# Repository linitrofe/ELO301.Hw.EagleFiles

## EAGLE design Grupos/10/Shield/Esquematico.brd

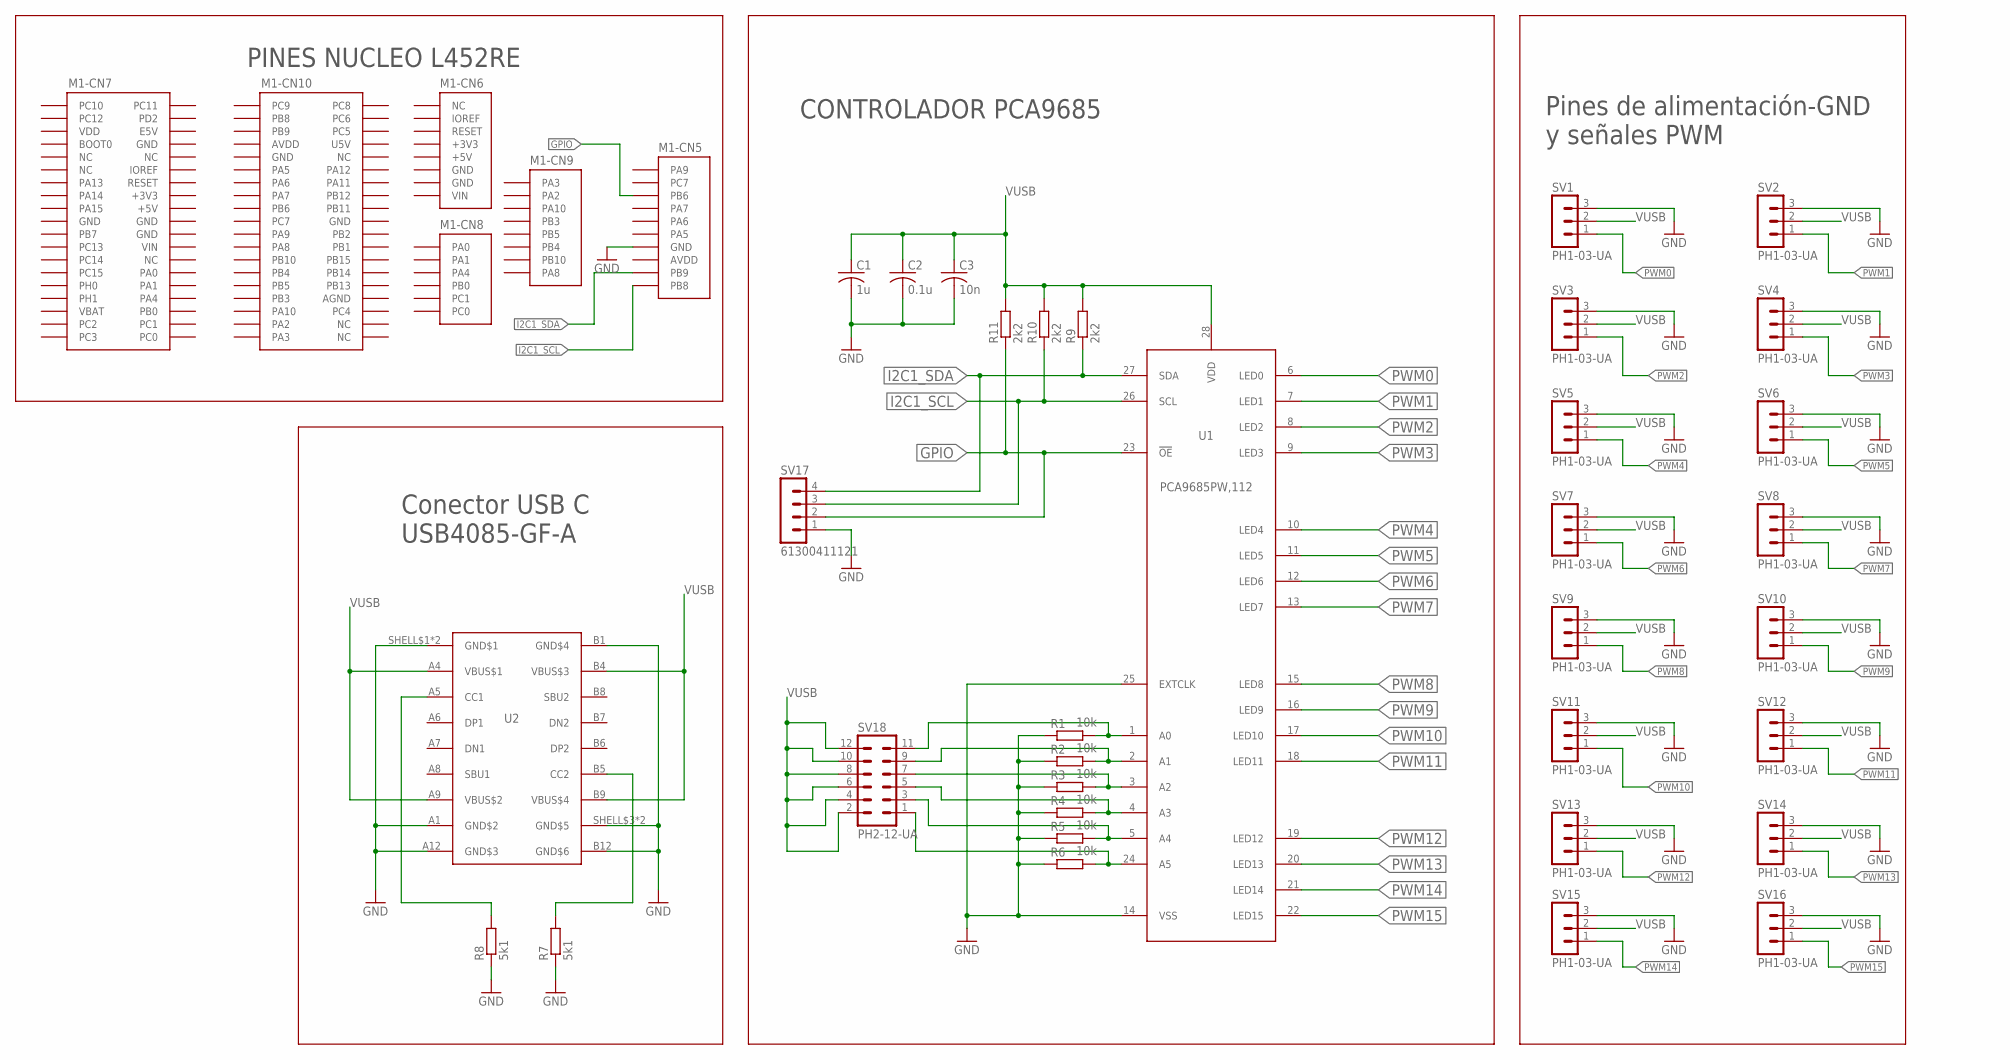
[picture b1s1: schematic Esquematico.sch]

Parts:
C1: 1u; C1206; PARTNO 490-5810-1-ND
C2: 0.1u; C0805; PARTNO 490-GCJ21BR72A104KA01KCT-ND
C3: 10n; C0603; PARTNO 490-4781-1-ND
M1: NUCLEO-L452RE; NUCLEO-64; PARTNO NUCLEO-L452RE
R1, R2, R3, R4, R5, R6: 10k; R0805; PARTNO 311-10KARCT-ND
R7, R8: 5k1; R0805; PARTNO 311-5.10KCRCT-ND
R9, R10, R11: 2k2; R0805; PARTNO 311-2.2KARCT-ND
SV1, SV2, SV3, SV4, SV5, SV6, SV7, SV8, SV9, SV10, SV11, SV12, SV13, SV14, SV15, SV16: PH1-03-UA; MA03-1; PARTNO PH1-03-UA
SV17: 61300411121; MA04-1; PARTNO 61300411121
SV18: PH2-12-UA; MA06-2; PARTNO PH2-12-UA
U1: PCA9685PW,112; SOP65P640X110-28N; PARTNO PCA9685PW,112
U2: USB4085-GF-A; TROUGH_HOLE; PARTNO 2073-USB4085-GF-ACT-ND

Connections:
+3V3: M1.CN6-4 (+3V3), M1.CN7-16 (+3V3)
+5V: M1.CN6-5 (+5V), M1.CN7-18 (+5V)
AGND: M1.CN10-32 (AGND)
AVDD: M1.CN5-8 (AVDD), M1.CN10-7 (AVDD)
GND: C1.2, C2.2, C3.2, M1.CN5-7 (GND), M1.CN6-6 (GND), M1.CN6-7 (GND), M1.CN7-8 (GND), M1.CN7-19 (GND), M1.CN7-20 (GND), M1.CN7-22 (GND), M1.CN10-9 (GND), M1.CN10-20 (GND), R1.1, R2.1, R3.1, R4.1, R5.1, R6.1, R7.1, R8.1, SV1.3, SV2.3, SV3.3, SV4.3, SV5.3, SV6.3, SV7.3, SV8.3, SV9.3, SV10.3, SV11.3, SV12.3, SV13.3, SV14.3, SV15.3, SV16.3, SV17.1, U1.14 (VSS), U1.25 (EXTCLK), U2.A1 (GND$2), U2.A12 (GND$3), U2.B1 (GND$4), U2.B12 (GND$6), U2.SHELL$1 (GND$1), U2.SHELL$2 (GND$1), U2.SHELL$3 (GND$5), U2.SHELL$4 (GND$5)
GPIO: M1.CN5-3 (PB6), R11.1, SV17.2, U1.23 (!OE)
I2C1_SCL: M1.CN5-10 (PB8), R10.1, SV17.3, U1.26 (SCL)
I2C1_SDA: M1.CN5-9 (PB9), R9.1, SV17.4, U1.27 (SDA)
IOREF: M1.CN6-2 (IOREF)
unnamed: R1.2, SV18.11, U1.1 (A0)
unnamed: R2.2, SV18.9, U1.2 (A1)
unnamed: R3.2, SV18.7, U1.3 (A2)
unnamed: R4.2, SV18.5, U1.4 (A3)
unnamed: R5.2, SV18.3, U1.5 (A4)
unnamed: R6.2, SV18.1, U1.24 (A5)
unnamed: R8.2, U2.A5 (CC1)
unnamed: R7.2, U2.B5 (CC2)
PWM0: SV1.1, U1.6 (LED0)
PWM1: SV2.1, U1.7 (LED1)
PWM2: SV3.1, U1.8 (LED2)
PWM3: SV4.1, U1.9 (LED3)
PWM4: SV5.1, U1.10 (LED4)
PWM5: SV6.1, U1.11 (LED5)
PWM6: SV7.1, U1.12 (LED6)
PWM7: SV8.1, U1.13 (LED7)
PWM8: SV9.1, U1.15 (LED8)
PWM9: SV10.1, U1.16 (LED9)
PWM10: SV11.1, U1.17 (LED10)
PWM11: SV12.1, U1.18 (LED11)
PWM12: SV13.1, U1.19 (LED12)
PWM13: SV14.1, U1.20 (LED13)
PWM14: SV15.1, U1.21 (LED14)
PWM15: SV16.1, U1.22 (LED15)
U5V: M1.CN10-8 (U5V)
VBAT: M1.CN7-33 (VBAT)
VDD: M1.CN7-5 (VDD)
VIN: M1.CN6-8 (VIN), M1.CN7-24 (VIN)
VUSB: C1.1, C2.1, C3.1, R9.2, R10.2, R11.2, SV1.2, SV2.2, SV3.2, SV4.2, SV5.2, SV6.2, SV7.2, SV8.2, SV9.2, SV10.2, SV11.2, SV12.2, SV13.2, SV14.2, SV15.2, SV16.2, SV18.2, SV18.4, SV18.6, SV18.8, SV18.10, SV18.12, U1.28 (VDD), U2.A4 (VBUS$1), U2.A9 (VBUS$2), U2.B4 (VBUS$3), U2.B9 (VBUS$4)

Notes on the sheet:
Pines de alimentación-GND y señales PWM
CONTROLADOR PCA9685
PINES NUCLEO L452RE
Conector USB C USB4085-GF-A

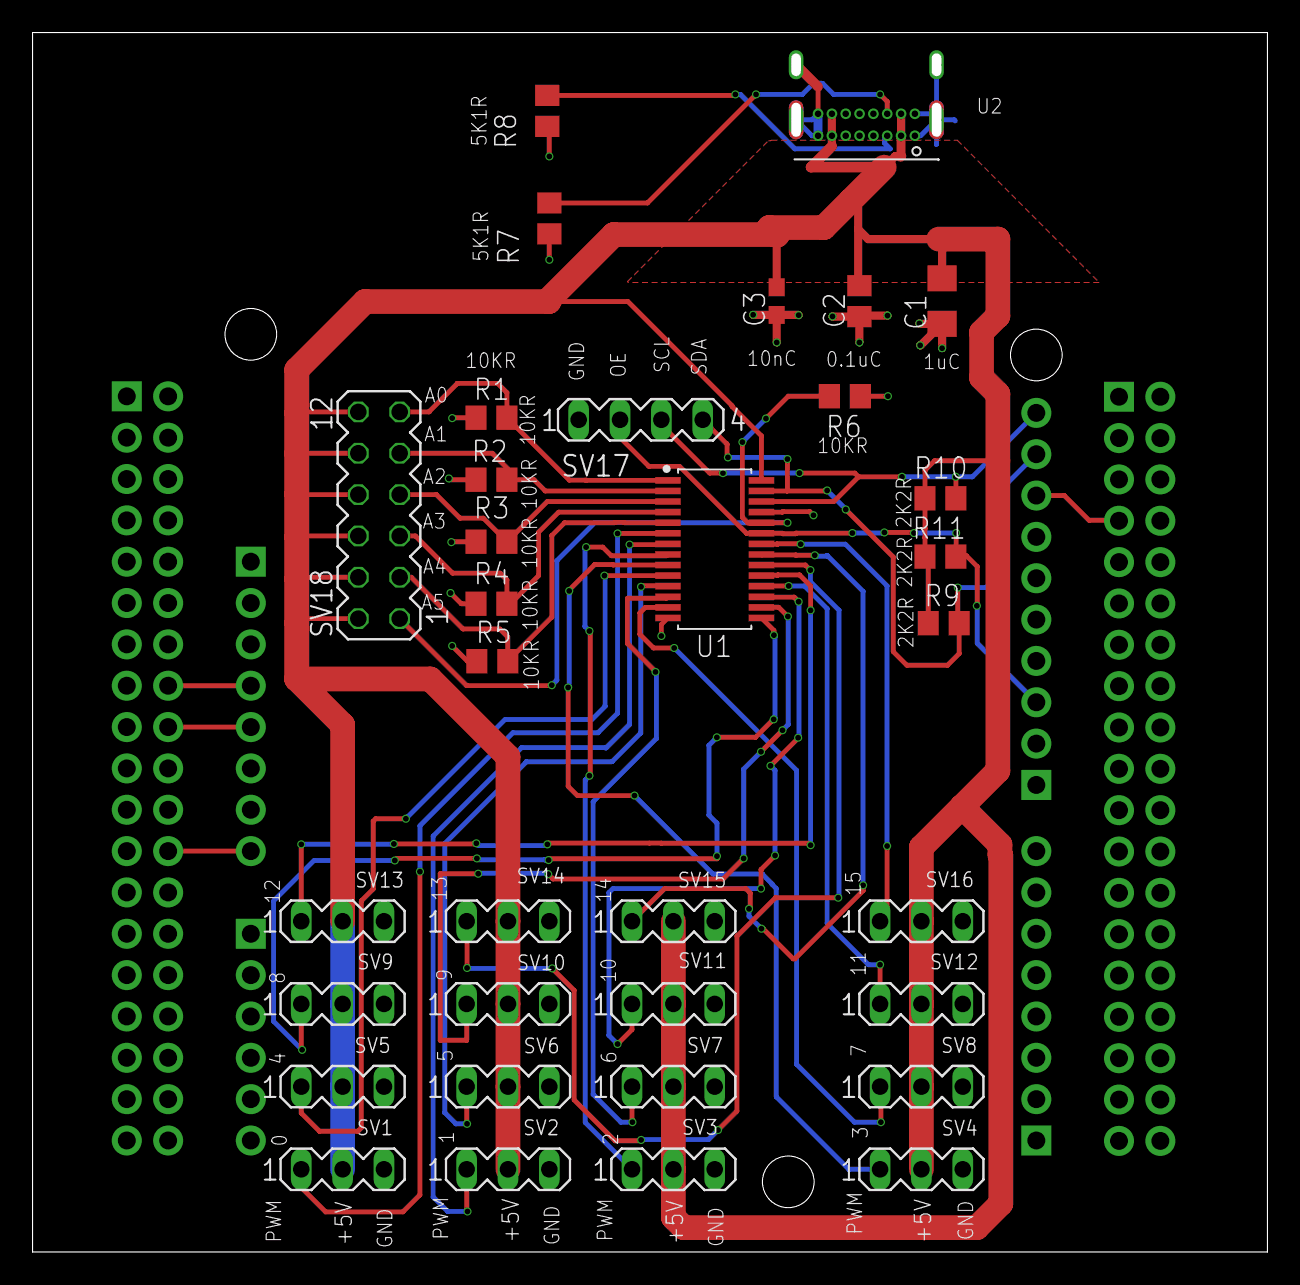
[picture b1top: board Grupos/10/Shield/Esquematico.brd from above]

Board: 2 copper layers, 75.9 x 74.9 mm, 35 parts (0 on the bottom side), 33 nets.

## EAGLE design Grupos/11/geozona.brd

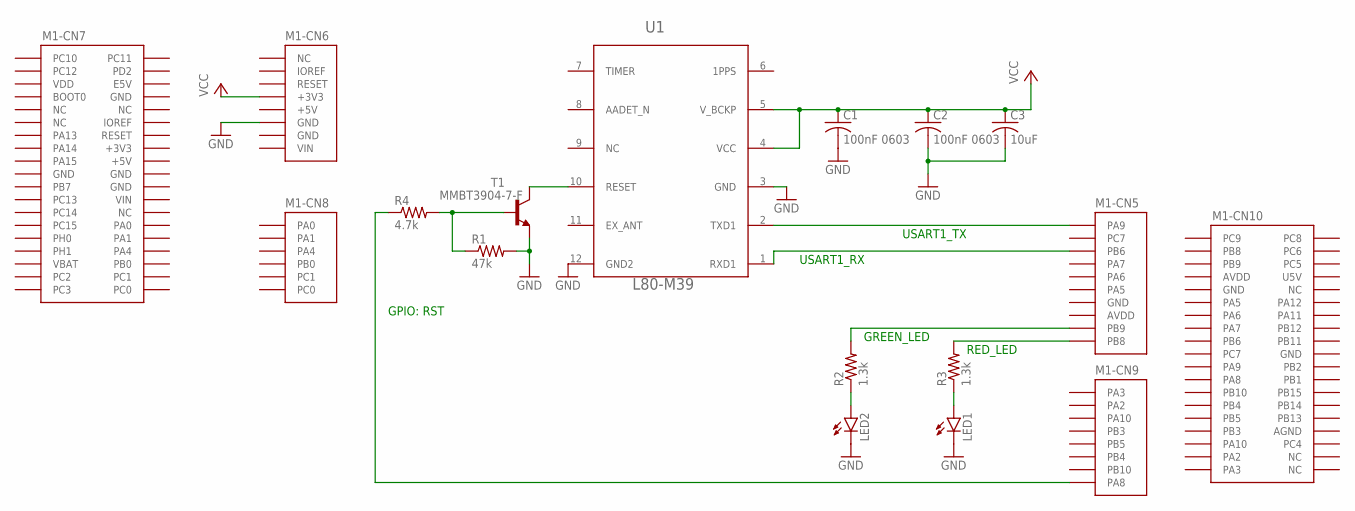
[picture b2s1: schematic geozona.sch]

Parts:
C1, C2: 100nF 0603; C0603; PARTNO GCJ188R71H104KA12D
C3: 10uF; C0805; PARTNO GRM21BR71A106KA73L
LED1: LED5MM; PARTNO C503B-RAN-CA0B0AA1
LED2: LED5MM; PARTNO C503B-GAN-CB0F0791
M1: NUCLEO-L452RE; NUCLEO-64; PARTNO ESP-WROOM-32
R1: 47k; R0805; PARTNO RC0805FR-0747KL
R2, R3: 1.3k; R0805; PARTNO RC0805FR-071K3L
R4: 4.7k; R0805; PARTNO RC0805JR-074K7L
T1: MMBT3904-7-F; SOT23; PARTNO MMBT3904-7-F
U1: L80-M39; 12-SMD; PARTNO L80-M39

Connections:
+3V3: M1.CN7-16 (+3V3)
+5V: M1.CN6-5 (+5V), M1.CN7-18 (+5V)
AGND: M1.CN10-32 (AGND)
AVDD: M1.CN5-8 (AVDD), M1.CN10-7 (AVDD)
GND: C1.2, C2.2, C3.2, LED1.K (C), LED2.K (C), M1.CN5-7 (GND), M1.CN6-6 (GND), M1.CN6-7 (GND), M1.CN7-8 (GND), M1.CN7-19 (GND), M1.CN7-20 (GND), M1.CN7-22 (GND), M1.CN10-9 (GND), M1.CN10-20 (GND), R1.2, T1.2 (E), U1.3 (GND), U1.12 (GND2)
IOREF: M1.CN6-2 (IOREF)
unnamed: M1.CN5-10 (PB8), R3.2
unnamed: T1.3 (C), U1.10 (RESET)
unnamed: R1.1, R4.2, T1.1 (B)
unnamed: M1.CN9-8 (PA8), R4.1
unnamed: LED2.A, R2.1
unnamed: M1.CN5-9 (PB9), R2.2
unnamed: LED1.A, R3.1
unnamed: M1.CN5-1 (PA9), U1.2 (TXD1)
unnamed: M1.CN5-3 (PB6), U1.1 (RXD1)
U5V: M1.CN10-8 (U5V)
VBAT: M1.CN7-33 (VBAT)
VCC: C1.1, C2.1, C3.1, M1.CN6-4 (+3V3), U1.4 (VCC), U1.5 (V_BCKP)
VDD: M1.CN7-5 (VDD)
VIN: M1.CN6-8 (VIN), M1.CN7-24 (VIN)

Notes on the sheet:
GREEN_LED
RED_LED
GPIO: RST
USART1_TX
USART1_RX

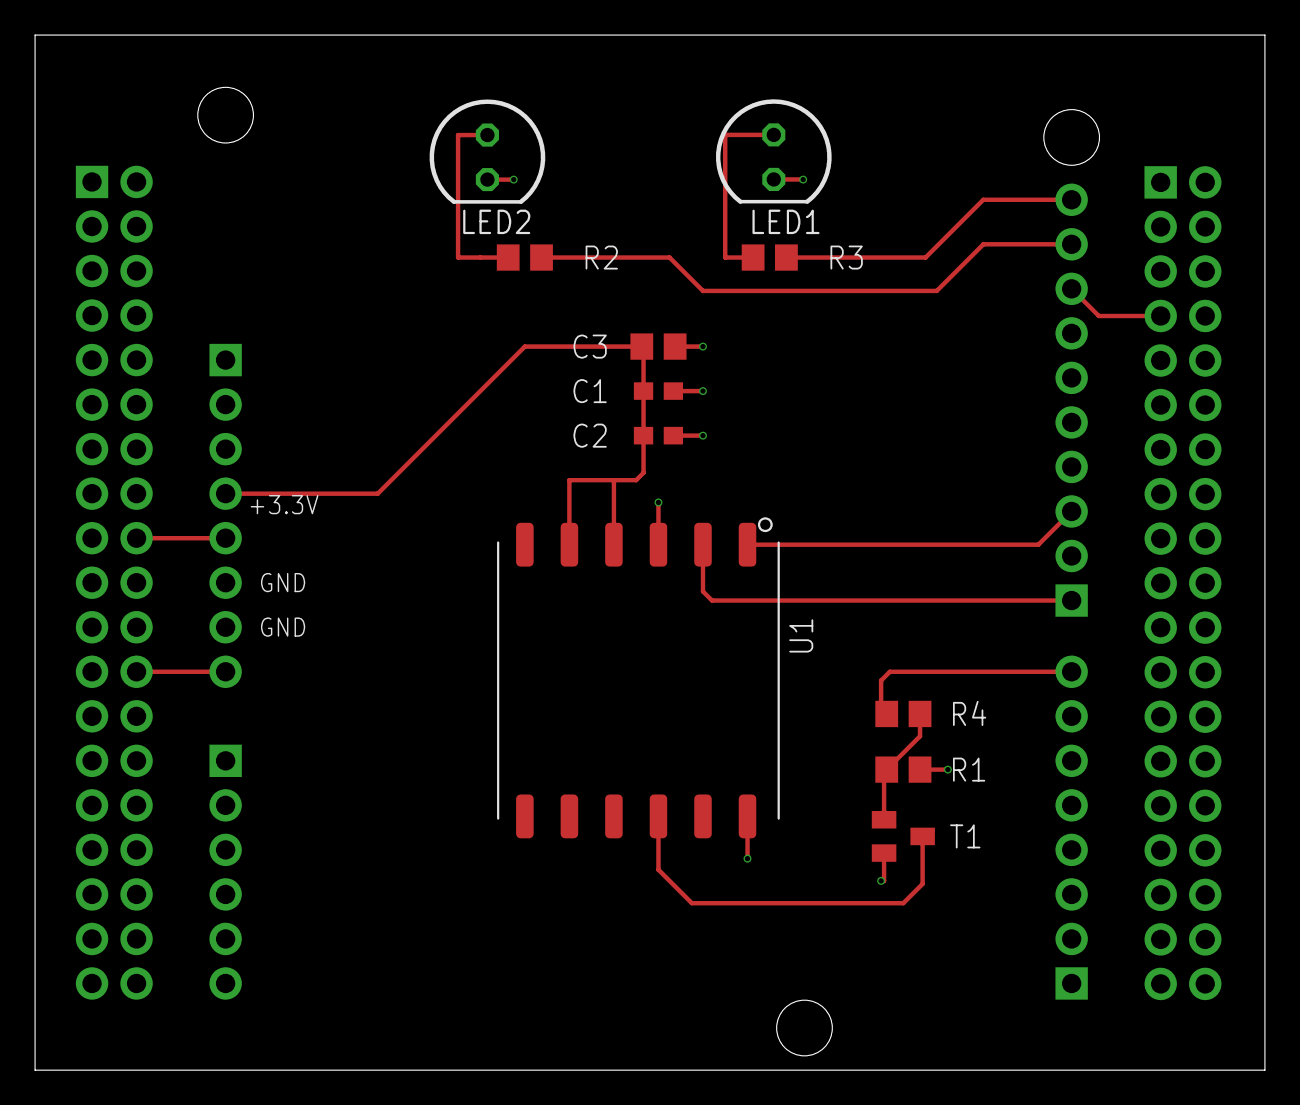
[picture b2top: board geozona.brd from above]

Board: 2 copper layers, 70.2 x 59.0 mm, 12 parts (0 on the bottom side), 14 nets.

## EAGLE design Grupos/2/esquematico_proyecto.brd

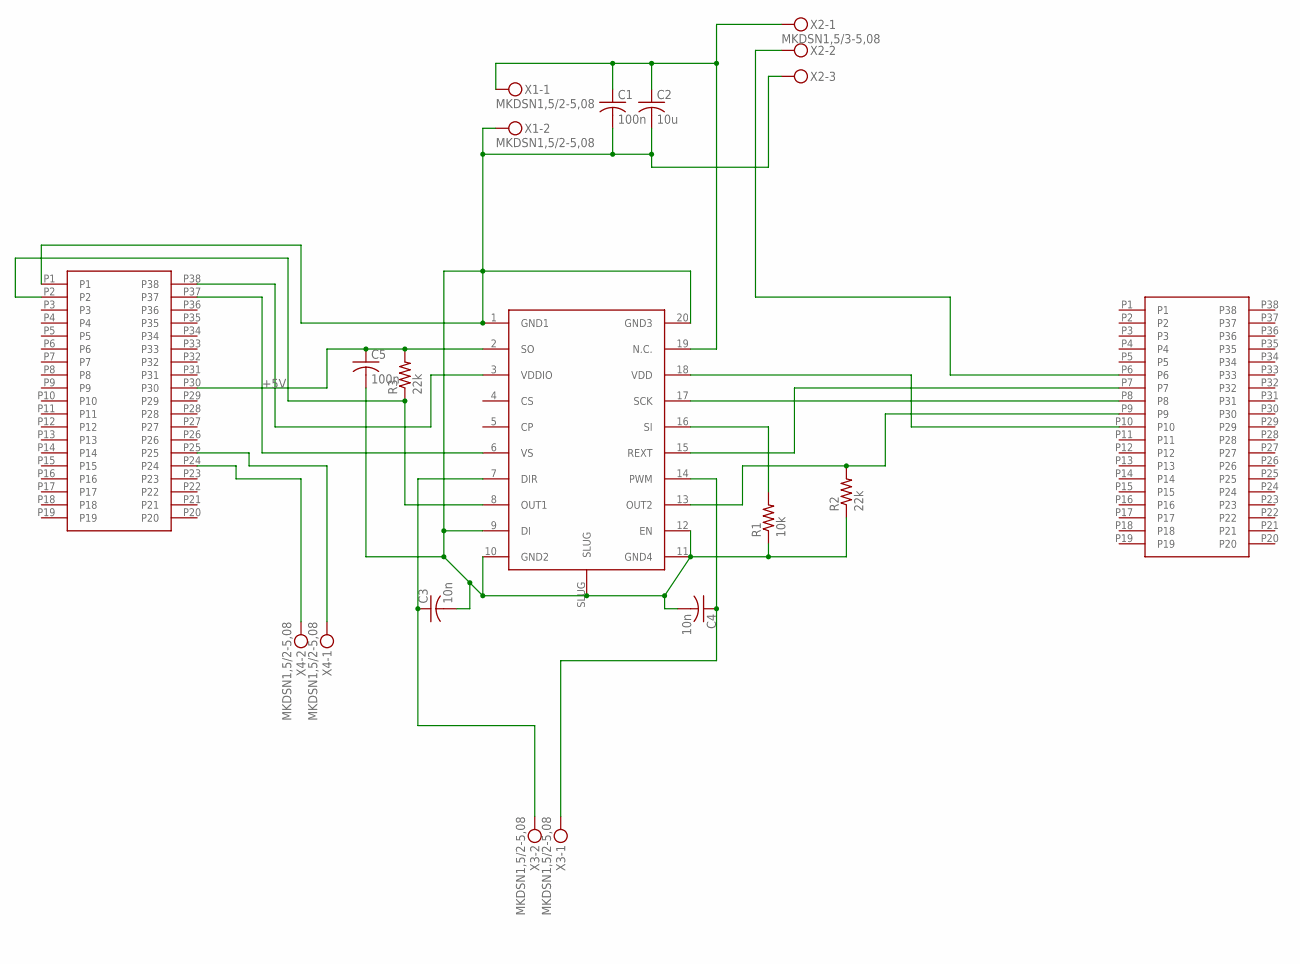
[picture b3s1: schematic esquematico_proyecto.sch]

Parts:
C1, C5: 100n; C0603
C2: 10u; C0805
C3, C4: 10n; C0201
R1: 10k; R0805
R2, R3: 22k; R0805
U$1: L9958L9958; L9958
U$2, U$3: PINHEADER
X1, X3, X4: MKDSN1,5/2-5,08
X2: MKDSN1,5/3-5,08

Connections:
+5V: C5.1, R3.2, U$1.2 (SO), U$2.P30
unnamed: R1.2, U$1.16 (SI)
unnamed: R2.2, U$1.13 (OUT2), U$3.P9
unnamed: C1.1, C2.1, U$1.19 (N.C.), X1.1, X2.1
unnamed: C3.1, U$1.7 (DIR), X3.2
unnamed: C4.1, U$1.14 (PWM), X3.1
unnamed: R3.1, U$1.8 (OUT1), U$2.P2
unnamed: U$3.P6, X2.2
unnamed: C1.2, C2.2, C3.2, C4.2, C5.2, R1.1, R2.1, U$1.1 (GND1), U$1.9 (DI), U$1.10 (GND2), U$1.11 (GND4), U$1.12 (EN), U$1.20 (GND3), U$1.SLUG, U$2.P1, X1.2, X2.3
unnamed: U$1.6 (VS), U$2.P37
unnamed: U$1.18 (VDD), U$3.P10
unnamed: U$1.17 (SCK), U$3.P8
unnamed: U$1.3 (VDDIO), U$2.P38
unnamed: U$1.15 (REXT), U$3.P7
unnamed: U$2.P25, X4.1
unnamed: U$2.P24, X4.2

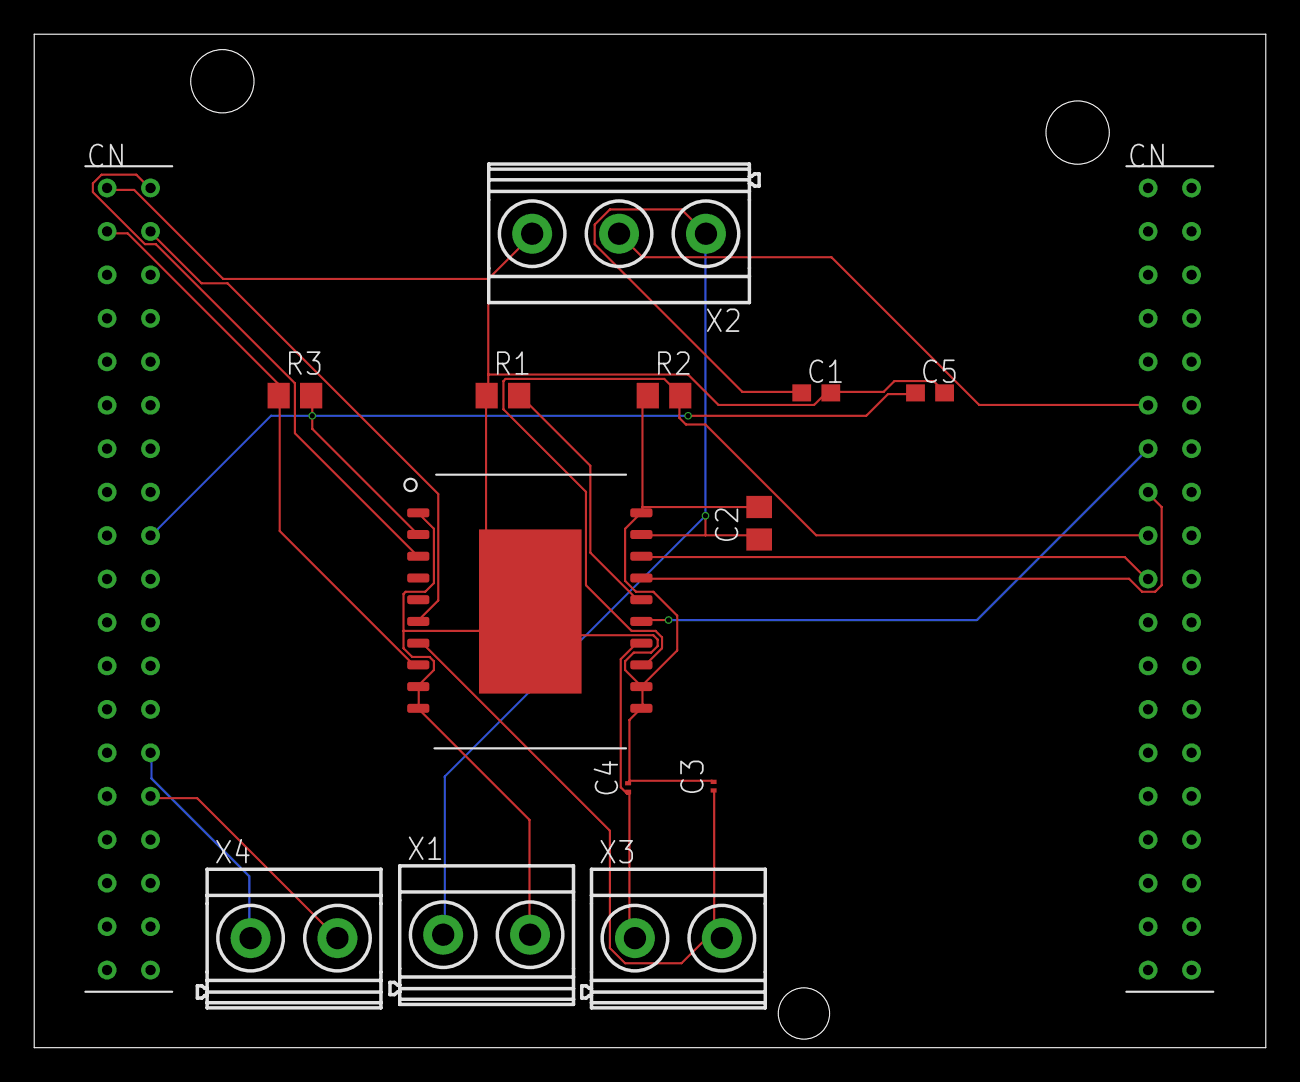
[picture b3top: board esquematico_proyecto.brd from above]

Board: 2 copper layers, 72.0 x 59.2 mm, 15 parts (0 on the bottom side), 16 nets.

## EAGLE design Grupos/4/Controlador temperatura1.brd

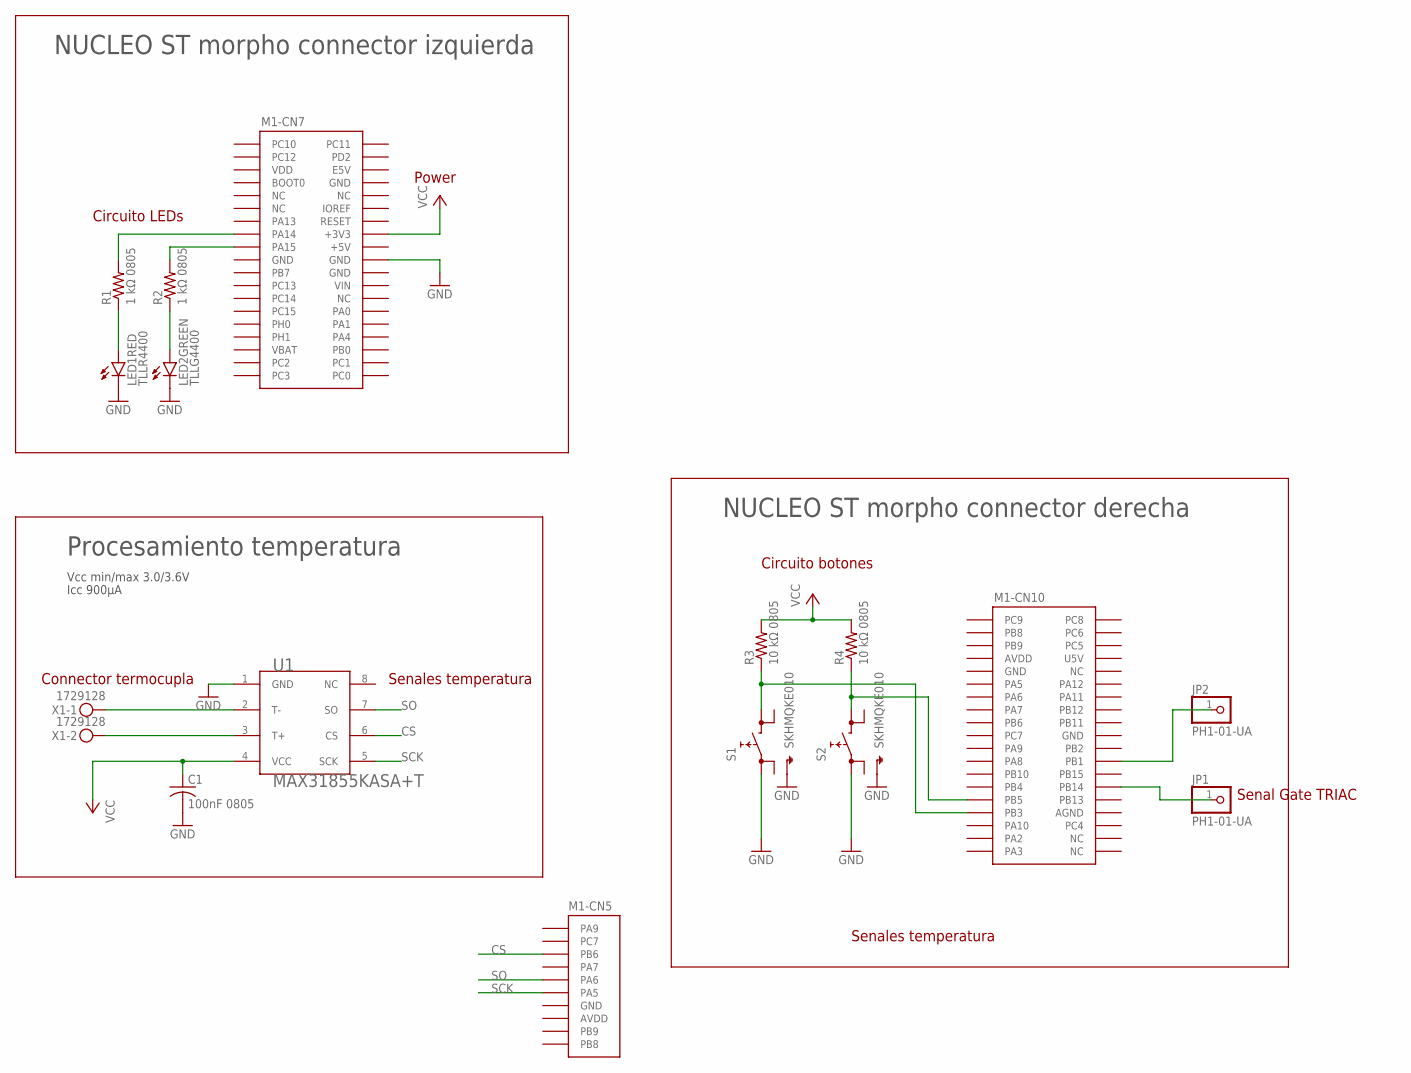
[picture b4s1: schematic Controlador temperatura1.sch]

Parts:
C1: 100nF 0805; C0805; PARTNO MA0805XR104K500
JP1, JP2: PH1-01-UA; 1X01; PARTNO PH1-01-UA
LED1RED: TLLR4400; LED3MM; PARTNO TLLR4400
LED2GREEN: TLLG4400; LED3MM; PARTNO TLLG4400
M1: NUCLEO-L452RE; NUCLEO-64
R1, R2: 1 kΩ 0805; R0805; PARTNO RC0805FR-071KL
R3, R4: 10 kΩ 0805; R0805; PARTNO RC0805FR-0710KL
S1, S2: SKHMQKE010; SKHMPXE010; PARTNO SKHMQKE010
U1: MAX31855KASA+T; PARTNO MAX31855KASA+T
X1: 1729128; MKDSN1,5/2-5,08; PARTNO 1729128

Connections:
+3V3: M1.CN6-4 (+3V3)
+5V: M1.CN6-5 (+5V), M1.CN7-18 (+5V)
AGND: M1.CN10-32 (AGND)
AVDD: M1.CN5-8 (AVDD), M1.CN10-7 (AVDD)
CS: M1.CN5-3 (PB6), U1.6 (CS)
GND: C1.2, LED1RED.K (C), LED2GREEN.K (C), M1.CN5-7 (GND), M1.CN6-6 (GND), M1.CN6-7 (GND), M1.CN7-8 (GND), M1.CN7-19 (GND), M1.CN7-20 (GND), M1.CN7-22 (GND), M1.CN10-9 (GND), M1.CN10-20 (GND), S1.1 (1.1), S1.5 (SH), S2.1 (1.1), S2.5 (SH), U1.1 (GND)
IOREF: M1.CN6-2 (IOREF)
unnamed: U1.2 (T-), X1.1
unnamed: U1.3 (T+), X1.2
unnamed: JP1.1, M1.CN10-28 (PB14)
unnamed: JP2.1, M1.CN10-24 (PB1)
unnamed: LED1RED.A, R1.1
unnamed: LED2GREEN.A, R2.1
unnamed: M1.CN7-15 (PA14), R1.2
unnamed: M1.CN7-17 (PA15), R2.2
unnamed: M1.CN10-31 (PB3), R3.1, S1.3 (2.1)
unnamed: M1.CN10-29 (PB5), R4.1, S2.3 (2.1)
SCK: M1.CN5-6 (PA5), U1.5 (SCK)
SO: M1.CN5-5 (PA6), U1.7 (SO)
U5V: M1.CN10-8 (U5V)
VBAT: M1.CN7-33 (VBAT)
VCC: C1.1, M1.CN7-16 (+3V3), R3.2, R4.2, U1.4 (VCC)
VDD: M1.CN7-5 (VDD)
VIN: M1.CN6-8 (VIN), M1.CN7-24 (VIN)

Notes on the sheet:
Procesamiento temperatura
Vcc min/max 3.0/3.6V
Icc 900µA
Connector termocupla
Senales temperatura
NUCLEO ST morpho connector izquierda
NUCLEO ST morpho connector derecha
Circuito botones
Senal Gate TRIAC
Circuito LEDs
Power

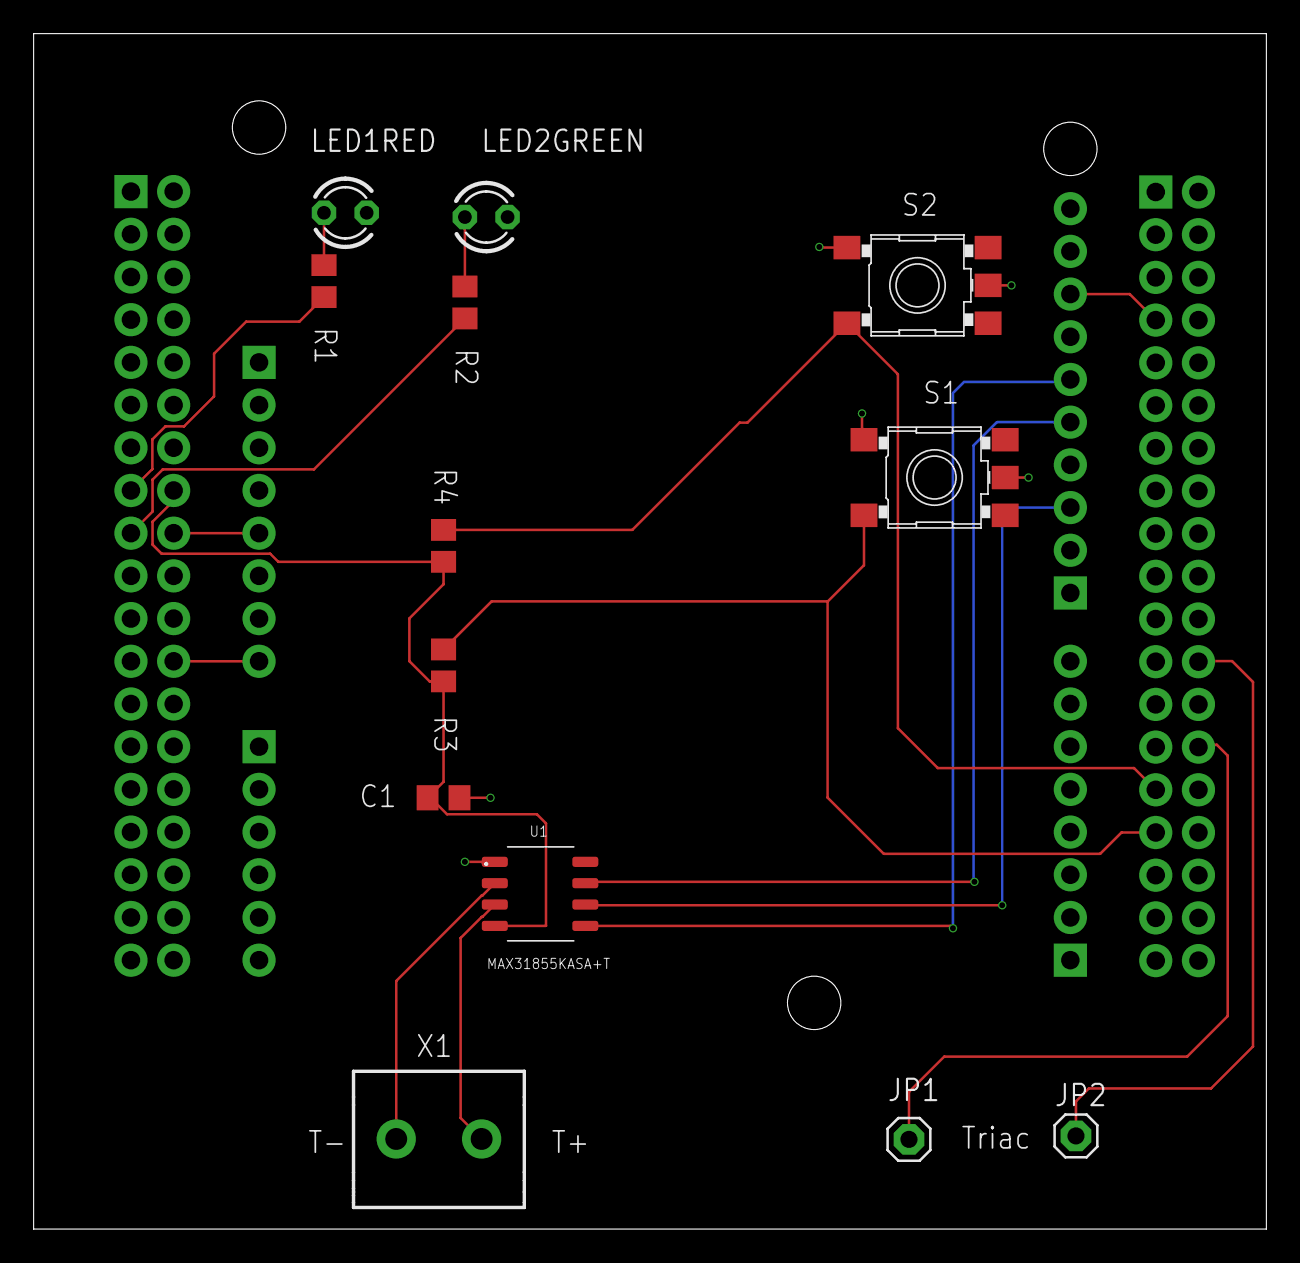
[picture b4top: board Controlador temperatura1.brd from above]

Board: 2 copper layers, 73.3 x 71.1 mm, 14 parts (0 on the bottom side), 18 nets.
